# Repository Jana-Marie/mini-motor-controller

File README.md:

# mini-motor-controller

A motor controller for miniature stepper motors, such as used in CD head drives. The additional ADC input allows for position feedback. This project was intended to be used in a DIY motor fader, however this motorfader has not been designed yet.

It features a cheap STM32F030 as brains with I2C as main IO to the host controller, an onboard regulator allows for an input voltage of up to 10V. The motor driver is a STSPIN220 with up to 1.3Arms.

<table>
  <tbody>
    <tr>
      <td colspan="2">
        
      </td>
    </tr>
    <tr>
      <td>
        
      </td>
      <td>
        
      </td>
    </tr>
    <tr>
      <td>
        
      </td>
      <td>
        
      </td>
    </tr>
  </tbody>
</table>

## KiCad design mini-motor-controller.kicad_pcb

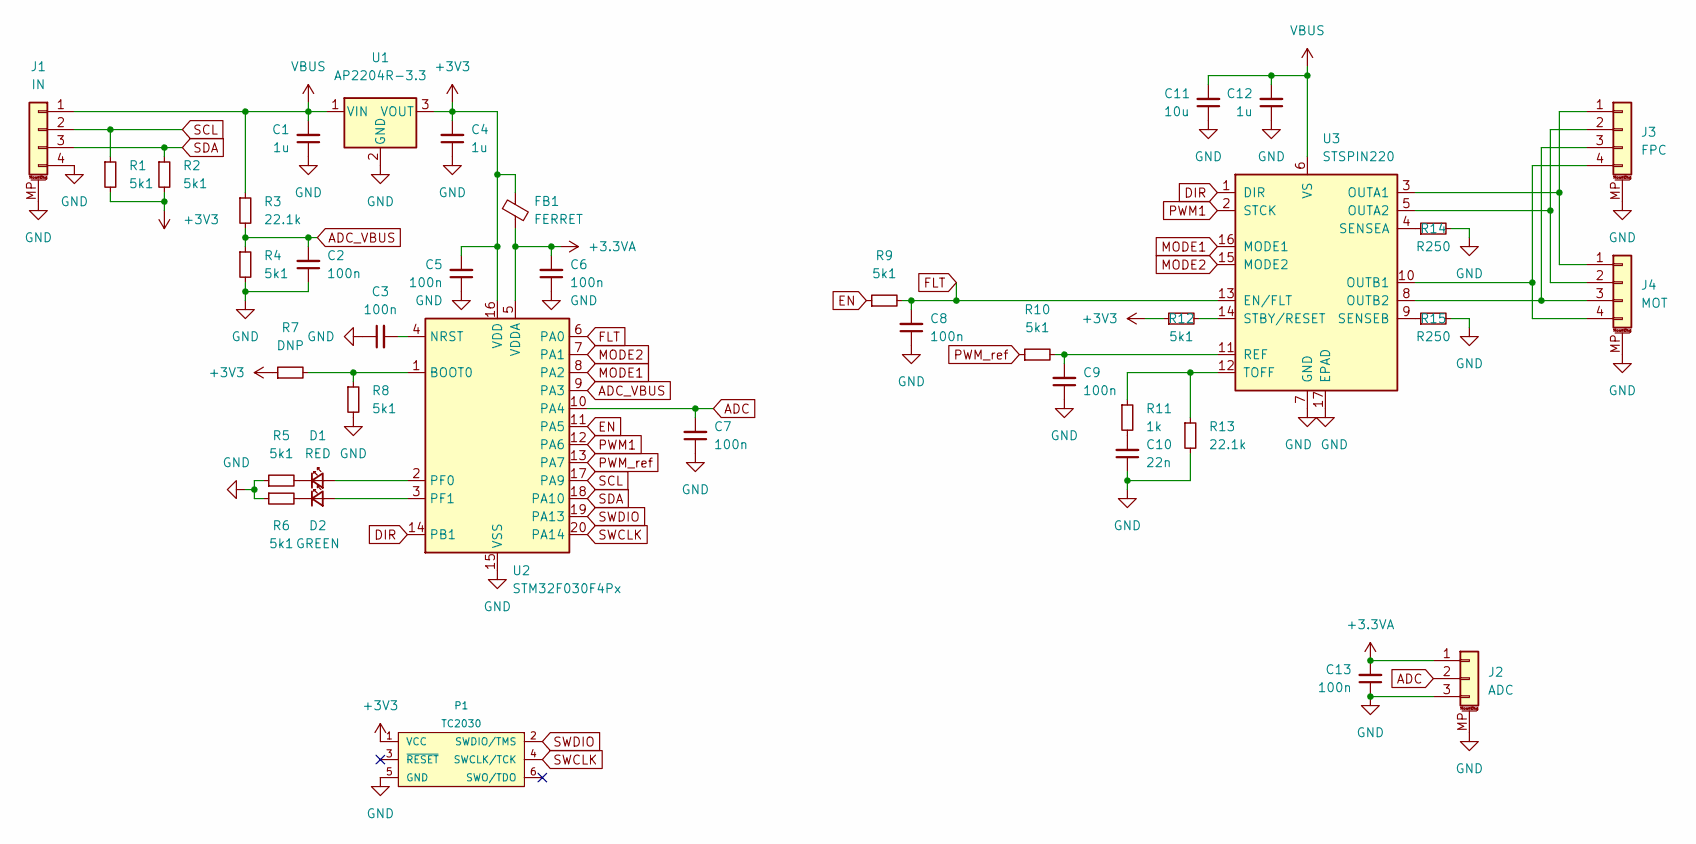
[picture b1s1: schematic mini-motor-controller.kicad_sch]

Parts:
C1, C4, C12: 1u; C_0603
C2, C3, C5, C6, C7, C8, C9, C13: 100n; C_0402
C10: 22n; C_0402
C11: 10u; C_0805
D1: RED; LED_0603_1608Metric
D2: GREEN; LED_0603_1608Metric
FB1: FERRET; R_0603
J1: IN; Molex_PicoBlade_53261-0471_1x04-1MP_P1.25mm_Horizontal
J2: ADC; Molex_PicoBlade_53261-0371_1x03-1MP_P1.25mm_Horizontal
J3: FPC; TE_84953-4_1x04-1MP_P1.0mm_Horizontal
J4: MOT; Molex_PicoBlade_53261-0471_1x04-1MP_P1.25mm_Horizontal
P1: TC2030
R1, R2, R4, R5, R6, R8, R9, R10, R12: 5k1; R_0402
R3, R13: 22.1k; R_0402
R7: DNP; R_0805
R11: 1k; R_0402
R14, R15: R250; R_0805
U1: AP2204R-3.3; SOT-89-3
U2: STM32F030F4Px; TSSOP-20_4.4x6.5mm_P0.65mm
U3: STSPIN220; VQFN-16-1EP_3x3mm_P0.5mm_EP1.8x1.8mm

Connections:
+3.3VA: C6.2, C13.2, FB1.2, J2.1, U2.5 (VDDA)
+3V3: C4.2, C5.2, FB1.1, P1.1 (VCC), R1.2, R2.2, R7.1, R12.1, U1.3 (VOUT), U2.16 (VDD)
ADC: C7.2, J2.2, U2.10 (PA4)
ADC_VBUS: C2.2, R3.2, R4.1, U2.9 (PA3)
DIR: U2.14 (PB1), U3.1 (DIR)
EN: R9.1, U2.11 (PA5)
FLT: C8.2, R9.2, U2.6 (PA0), U3.13 (EN/FLT)
GND: C1.1, C2.1, C3.1, C4.1, C5.1, C6.1, C7.1, C8.1, C9.1, C10.1, C11.1, C12.1, C13.1, J1.4, J1.MP (MountPin), J2.3, J2.MP (MountPin), J3.MP (MountPin), J4.MP (MountPin), P1.5 (GND), R4.2, R5.1, R6.1, R8.2, R13.2, R14.2, R15.2, U1.2 (GND), U2.15 (VSS), U3.7 (GND), U3.17 (EPAD)
MODE1: U2.8 (PA2), U3.16 (MODE1)
MODE2: U2.7 (PA1), U3.15 (MODE2)
unnamed: C3.2, U2.4 (NRST)
unnamed: C9.2, R10.2, U3.11 (REF)
unnamed: C10.2, R11.2
unnamed: D1.1 (K), R5.2
unnamed: D1.2 (A), U2.2 (PF0)
unnamed: D2.1 (K), R6.2
unnamed: D2.2 (A), U2.3 (PF1)
unnamed: J3.1, J4.1, U3.3 (OUTA1)
unnamed: J3.2, J4.2, U3.5 (OUTA2)
unnamed: R7.2, R8.1, U2.1 (BOOT0)
unnamed: R11.1, R13.1, U3.12 (TOFF)
unnamed: R12.2, U3.14 (STBY/RESET)
unnamed: R14.1, U3.4 (SENSEA)
unnamed: R15.1, U3.9 (SENSEB)
unnamed: J3.3, J4.3, U3.8 (OUTB2)
unnamed: J3.4, J4.4, U3.10 (OUTB1)
PWM1: U2.12 (PA6), U3.2 (STCK)
PWM_ref: R10.1, U2.13 (PA7)
SCL: J1.2, R1.1, U2.17 (PA9)
SDA: J1.3, R2.1, U2.18 (PA10)
SWCLK: P1.4 (SWCLK/TCK), U2.20 (PA14)
SWDIO: P1.2 (SWDIO/TMS), U2.19 (PA13)
VBUS: C1.2, C11.2, C12.2, J1.1, R3.1, U1.1 (VIN), U3.6 (VS)

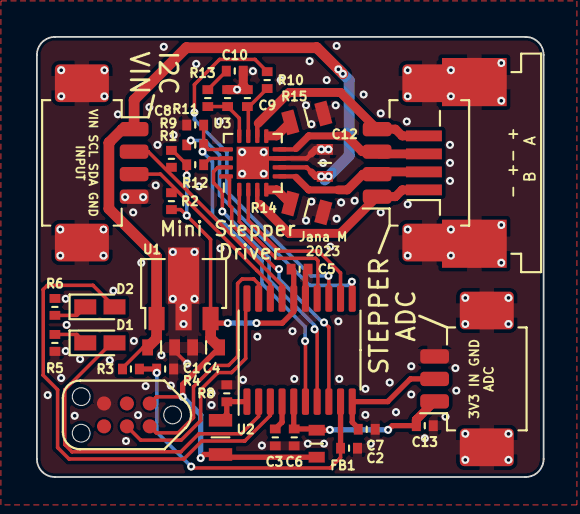
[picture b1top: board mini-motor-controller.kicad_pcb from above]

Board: 2 copper layers, 28.2 x 24.5 mm, 39 parts (1 on the bottom side), 33 nets.

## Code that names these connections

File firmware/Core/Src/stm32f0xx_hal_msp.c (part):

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
    __HAL_RCC_GPIOA_CLK_ENABLE();
    /**ADC GPIO Configuration
    PA3     ------> ADC_IN3
    PA4     ------> ADC_IN4
    */
    GPIO_InitStruct.Pin = GPIO_PIN_3|GPIO_PIN_4;
    GPIO_InitStruct.Mode = GPIO_MODE_ANALOG;
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    __HAL_RCC_ADC1_CLK_DISABLE();

    /**ADC GPIO Configuration
    PA3     ------> ADC_IN3
    PA4     ------> ADC_IN4
    */
    HAL_GPIO_DeInit(GPIOA, GPIO_PIN_3|GPIO_PIN_4);

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
    __HAL_RCC_GPIOA_CLK_ENABLE();
    /**I2C1 GPIO Configuration
    PA9     ------> I2C1_SCL
    PA10     ------> I2C1_SDA
    */
    GPIO_InitStruct.Pin = GPIO_PIN_9|GPIO_PIN_10;
    GPIO_InitStruct.Mode = GPIO_MODE_AF_OD;
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    __HAL_RCC_I2C1_CLK_DISABLE();

    /**I2C1 GPIO Configuration
    PA9     ------> I2C1_SCL
    PA10     ------> I2C1_SDA
    */
    HAL_GPIO_DeInit(GPIOA, GPIO_PIN_9);

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  /* USER CODE END TIM3_MspPostInit 0 */
    __HAL_RCC_GPIOA_CLK_ENABLE();
    /**TIM3 GPIO Configuration
    PA6     ------> TIM3_CH1
    */
    GPIO_InitStruct.Pin = GPIO_PIN_6;
    GPIO_InitStruct.Mode = GPIO_MODE_AF_PP;
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
    __HAL_RCC_GPIOA_CLK_ENABLE();
    /**TIM14 GPIO Configuration
    PA7     ------> TIM14_CH1
    */
    GPIO_InitStruct.Pin = GPIO_PIN_7;
    GPIO_InitStruct.Mode = GPIO_MODE_AF_PP;
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
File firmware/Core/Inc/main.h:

/* USER CODE BEGIN Header */
/**
  ******************************************************************************
  * @file           : main.h
  * @brief          : Header for main.c file.
  *                   This file contains the common defines of the application.
  ******************************************************************************
  * @attention
  *
  * Copyright (c) 2023 STMicroelectronics.
  * All rights reserved.
  *
  * This software is licensed under terms that can be found in the LICENSE file
  * in the root directory of this software component.
  * If no LICENSE file comes with this software, it is provided AS-IS.
  *
  ******************************************************************************
  */
/* USER CODE END Header */

/* Define to prevent recursive inclusion -------------------------------------*/
#ifndef __MAIN_H
#define __MAIN_H

#ifdef __cplusplus
extern "C" {
#endif

/* Includes ------------------------------------------------------------------*/
#include "stm32f0xx_hal.h"

/* Private includes ----------------------------------------------------------*/
/* USER CODE BEGIN Includes */

/* USER CODE END Includes */

/* Exported types ------------------------------------------------------------*/
/* USER CODE BEGIN ET */

/* USER CODE END ET */

/* Exported constants --------------------------------------------------------*/
/* USER CODE BEGIN EC */

/* USER CODE END EC */

/* Exported macro ------------------------------------------------------------*/
/* USER CODE BEGIN EM */

/* USER CODE END EM */

void HAL_TIM_MspPostInit(TIM_HandleTypeDef *htim);

/* Exported functions prototypes ---------------------------------------------*/
void Error_Handler(void);

/* USER CODE BEGIN EFP */

/* USER CODE END EFP */

/* Private defines -----------------------------------------------------------*/
#define LED_ERR_Pin GPIO_PIN_0
#define LED_ERR_GPIO_Port GPIOF
#define LED_OK_Pin GPIO_PIN_1
#define LED_OK_GPIO_Port GPIOF
#define FAULT_Pin GPIO_PIN_0
#define FAULT_GPIO_Port GPIOA
#define MODE2_Pin GPIO_PIN_1
#define MODE2_GPIO_Port GPIOA
#define MODE1_Pin GPIO_PIN_2
#define MODE1_GPIO_Port GPIOA
#define EN_Pin GPIO_PIN_5
#define EN_GPIO_Port GPIOA
#define STEP_Pin GPIO_PIN_6
#define STEP_GPIO_Port GPIOA
#define PWM_ref_Pin GPIO_PIN_7
#define PWM_ref_GPIO_Port GPIOA
#define DIR_Pin GPIO_PIN_1
#define DIR_GPIO_Port GPIOB
/* USER CODE BEGIN Private defines */

/* USER CODE END Private defines */

#ifdef __cplusplus
}
#endif

#endif /* __MAIN_H */

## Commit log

2023-01-02 added gitignore
2023-01-02 added source files
2023-01-02 added License
2023-01-02 added readme
2025-08-13 ammended gitignore
2025-08-13 bumped files
2025-08-13 added firmware
2025-08-13 moved images
2025-08-13 added gif
2025-08-13 added schematic
2025-08-13 updated schematic
2025-08-13 fixed typo
